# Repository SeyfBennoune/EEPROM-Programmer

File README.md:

# 1. Overview   
  
  This project was part of the Z80 computer project (found in "Z80Computer" repo), where this EEPROM programmer was used intensively in programming that project's EEPROM chips.   
  This project is continuously enhanced whenever possible.  
     
# 2. History and Future enhancement   
   
  ## 2.1 History
  * First, Arduino Uno was used to build the first prototype for this project.  
  * Arduino Uno was replaced later with Arduino Nano for the sake of minimising dimensions.  
  * For GUI, Arduino IDE's serial monitor was used to communicate serially with the device.
  * A C program is built later using gtk toolkit.
  ## 2.2 What's next?
  * Replacing arduino dev board with a microcontroller chip as a chalenge where the level of abstraction is lowered.  
  * Building a GUI using Flutter framework as a learning project.

# 3. Circuit
  ## 3.1 Schematics   

  ## 3.2 PCB preview

# 4. GUI   

# 5. Notes
Relevant Kicad files and C program will be uploaded soon.

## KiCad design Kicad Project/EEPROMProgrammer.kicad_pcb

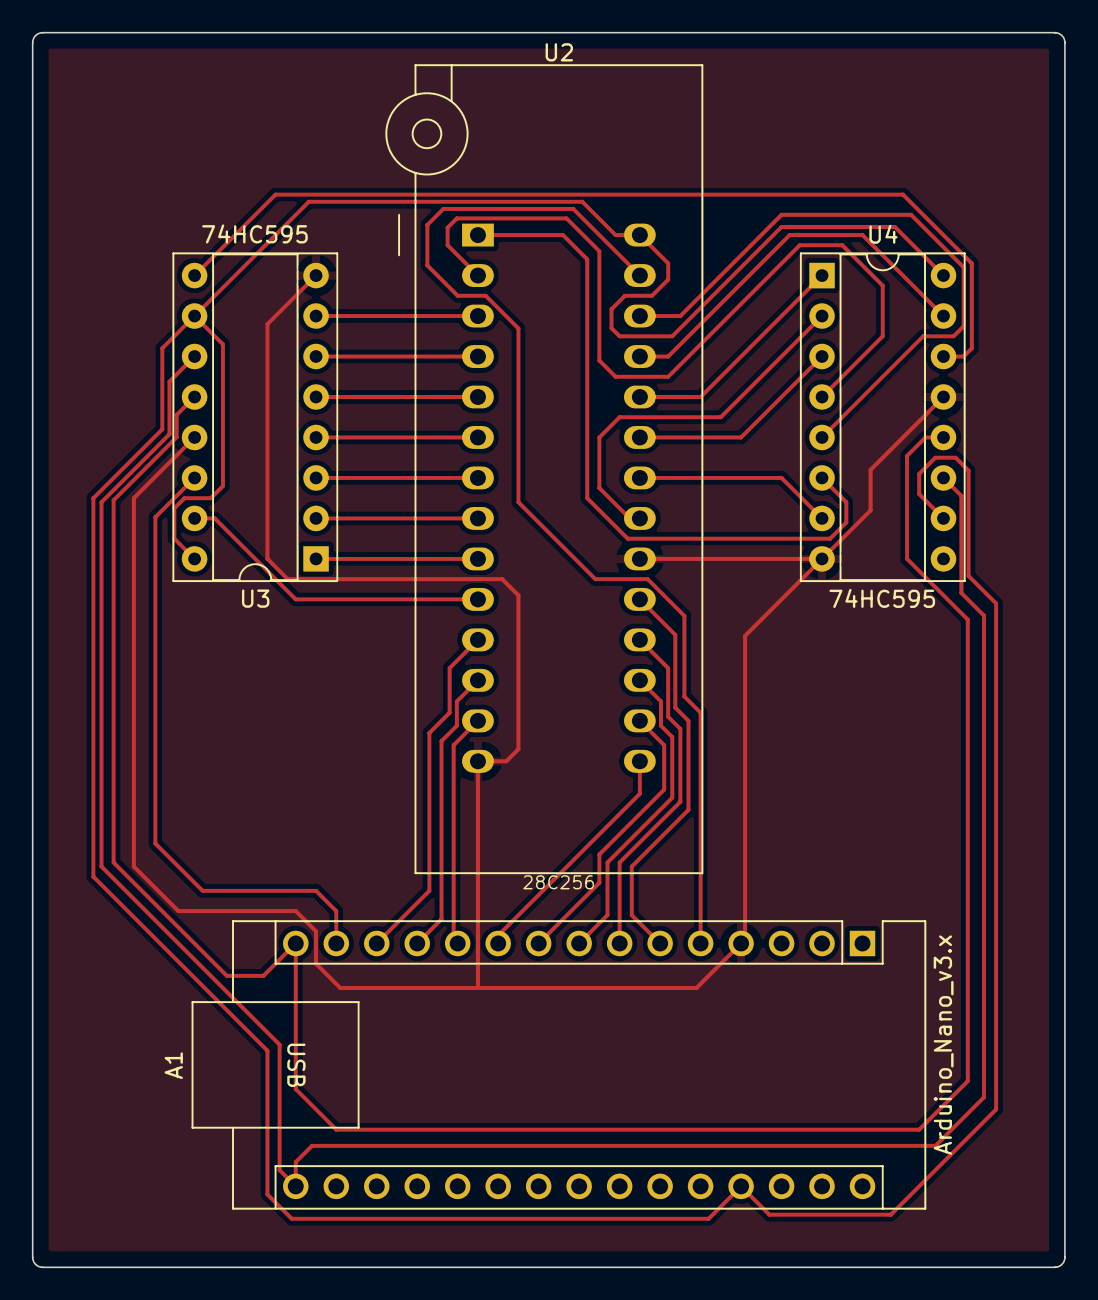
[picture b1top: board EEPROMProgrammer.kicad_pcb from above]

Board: 2 copper layers, 64.8 x 77.5 mm, 4 parts (0 on the bottom side), 31 nets.

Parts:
A1: Arduino_Nano_v3.x; Arduino_Nano
U2: 28C256; DIP_Socket-28_W6.9_W7.62_W10.16_W12.7_W13.5_3M_228-4817-00-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
U3, U4: 74HC595; DIP-16_W7.62mm_Socket

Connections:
/A0: U2.10 (A0), U3.15 (QA)
/A1: U2.9 (A1), U3.1 (QB)
/A2: U2.8 (A2), U3.2 (QC)
/A3: U2.7 (A3), U3.3 (QD)
/A4: U2.6 (A4), U3.4 (QE)
/A5: U2.5 (A5), U3.5 (QF)
/A6: U2.4 (A6), U3.6 (QG)
/A7: U2.3 (A7), U3.7 (QH)
/A8: U2.25 (A8), U4.15 (QA)
/A9: U2.24 (A9), U4.1 (QB)
/A10: U2.21 (A10), U4.2 (QC)
/A11: U2.23 (A11), U4.3 (QD)
/A12: U2.2 (A12), U4.4 (QE)
/A13: U2.26 (A13), U4.5 (QF)
/A14: U2.1 (A14), U4.6 (QG)
/D0: A1.13 (D10), U2.11 (D0)
/D1: A1.12 (D9), U2.12 (D1)
/D2: A1.11 (D8), U2.13 (D2)
/D3: A1.10 (D7), U2.15 (D3)
/D4: A1.9 (D6), U2.16 (D4)
/D5: A1.8 (D5), U2.17 (D5)
/D6: A1.7 (D4), U2.18 (D6)
/D7: A1.6 (D3), U2.19 (D7)
/QH': U3.9 (QH'), U4.14 (SER)
GND: A1.4 (GND), U2.14 (GND), U2.20 (~CS), U3.8 (GND), U3.13 (~OE), U4.8 (GND), U4.13 (~OE)
RCLK: A1.15 (D12), U3.12 (RCLK), U4.12 (RCLK)
SER: A1.14 (D11), U3.14 (SER)
SRCLK: A1.16 (D13), U3.11 (SRCLK), U4.11 (SRCLK)
VCC: A1.27 (+5V), U2.28 (VCC), U3.10 (~SRCLR), U3.16 (VCC), U4.10 (~SRCLR), U4.16 (VCC)
~OE: U2.22 (~OE), U4.7 (QH)
~WR: A1.5 (D2), U2.27 (~WE)

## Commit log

2023-09-15 Uploaded Kicad files
2023-09-15 Kicad files uploaded
